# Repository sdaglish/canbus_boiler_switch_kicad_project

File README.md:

# Canbus Boiler Switch KiCad Project

## Version History

* v1.0
    * 23 Feb 2020
        * First manufactured prototype of board
        * Developed for prototyping
        * Developed for extending to sensor, ect. via header pins
* v1.1
    * 23 Feb 2020
        * Adding version history to readme
        * Removed mfr files from project
        * Removed backup files from project
        * Added sheet information to schematic files

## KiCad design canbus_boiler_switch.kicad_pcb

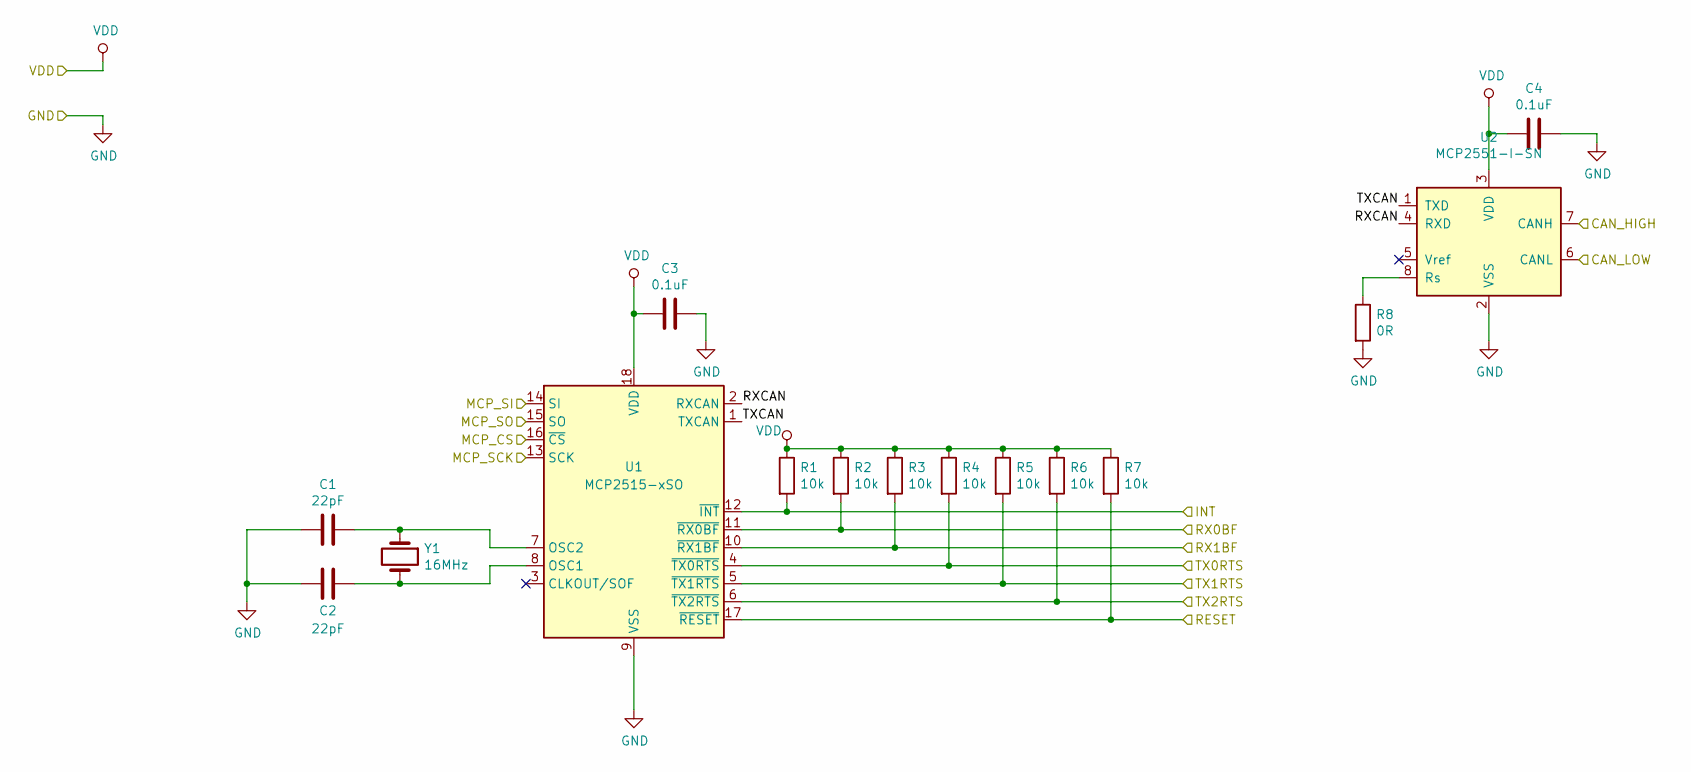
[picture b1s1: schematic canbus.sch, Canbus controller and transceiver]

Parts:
C1, C2: 22pF; C_1206_3216Metric
C3, C4: 0.1uF; C_1206_3216Metric
R1, R2, R3, R4, R5, R6, R7: 10k; R_1206_3216Metric
R8: 0R; R_1206_3216Metric
U1: MCP2515-xSO; SOIC-18W_7.5x11.6mm_P1.27mm
U2: MCP2551-I-SN; SOIC-8_3.9x4.9mm_P1.27mm
Y1: 16MHz; Crystal_SMD_HC49-SD_HandSoldering

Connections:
/canbus/INT: R1.2, U1.12 (~INT); also elsewhere on the board
/canbus/MCP_SCK: U1.13 (SCK); also elsewhere on the board
/canbus/MCP_SI: U1.14 (SI); also elsewhere on the board
/canbus/MCP_SO: U1.15 (SO); also elsewhere on the board
/canbus/RESET: R7.2, U1.17 (~RESET); also elsewhere on the board
/canbus/RX0BF: R2.2, U1.11 (~RX0BF); also elsewhere on the board
/canbus/RX1BF: R3.2, U1.10 (~RX1BF); also elsewhere on the board
/canbus/RXCAN: U1.2 (RXCAN), U2.4 (RXD)
/canbus/TX0RTS: R4.2, U1.4 (~TX0RTS); also elsewhere on the board
/canbus/TX1RTS: R5.2, U1.5 (~TX1RTS); also elsewhere on the board
/canbus/TX2RTS: R6.2, U1.6 (~TX2RTS); also elsewhere on the board
/canbus/TXCAN: U1.1 (TXCAN), U2.1 (TXD)
/mircoprocessor/CS: U1.16 (~CS); also elsewhere on the board
/rj12_connections/CAN_H: U2.7 (CANH); also elsewhere on the board
/rj12_connections/CAN_L: U2.6 (CANL); also elsewhere on the board
GND: C1.2, C2.2, C3.1, C4.1, R8.2, U1.9 (VSS), U2.2 (VSS); also elsewhere on the board
unnamed: C1.1, U1.7 (OSC2), Y1.1
unnamed: C2.1, U1.8 (OSC1), Y1.2
unnamed: R8.1, U2.8 (Rs)
VDD: C3.2, C4.2, R1.1, R2.1, R3.1, R4.1, R5.1, R6.1, R7.1, U1.18 (VDD), U2.3 (VDD); also elsewhere on the board

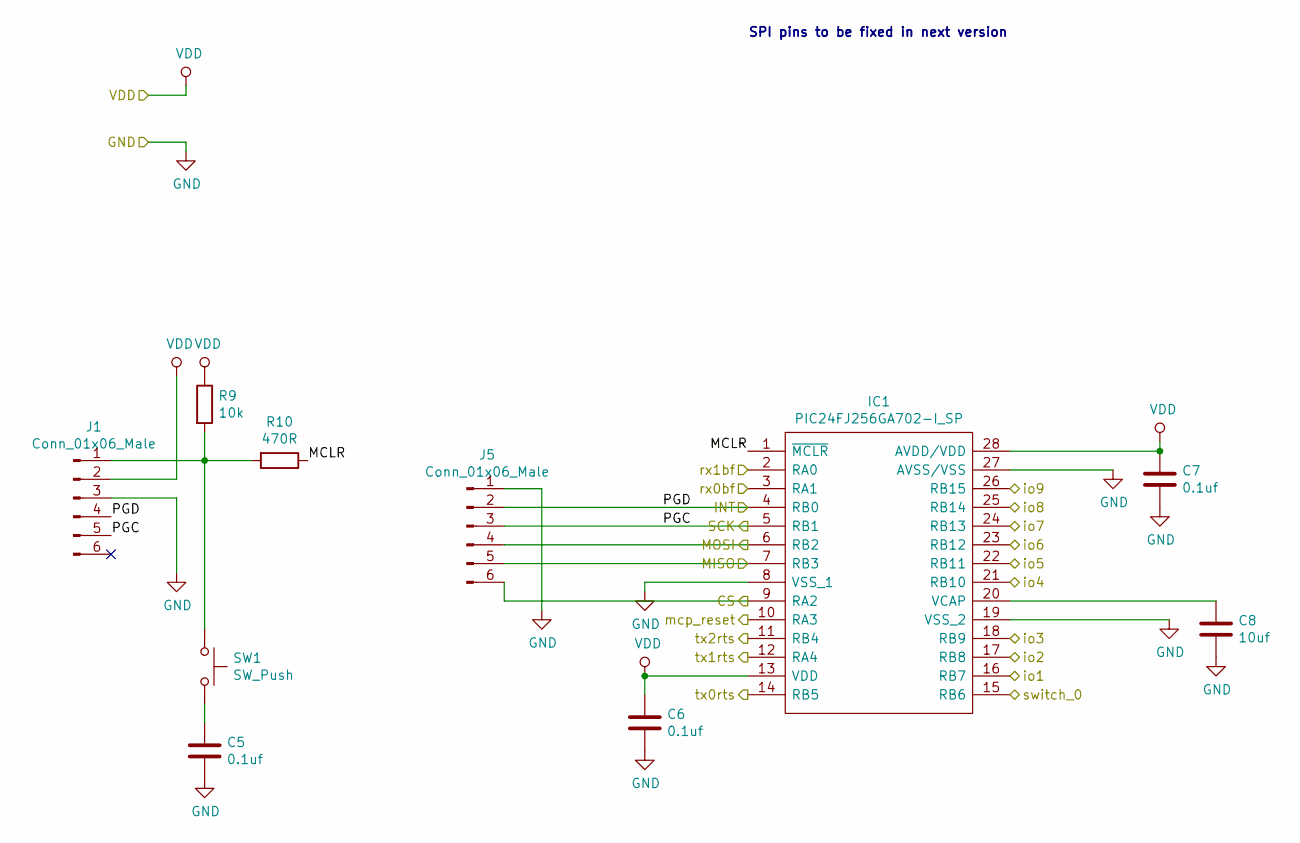
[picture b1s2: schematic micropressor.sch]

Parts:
C5, C6, C7: 0.1uf; C_1206_3216Metric
C8: 10uf; C_1206_3216Metric
IC1: PIC24FJ256GA702-I_SP; SOIC127P1030X265-28N; Manufacturer_Part_Number PIC24FJ256GA702-I/SP; Mouser Part Number 579-24FJ256GA702ISP
J1, J5: Conn_01x06_Male; PinHeader_1x06_P2.54mm_Vertical
R9: 10k; R_1206_3216Metric
R10: 470R; R_1206_3216Metric
SW1: SW_Push; SW_PUSH_6mm

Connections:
/canbus/INT: IC1.4 (RB0), J1.4, J5.2; also elsewhere on the board
/canbus/MCP_SCK: IC1.5 (RB1), J1.5, J5.3; also elsewhere on the board
/canbus/MCP_SI: IC1.6 (RB2), J5.4; also elsewhere on the board
/canbus/MCP_SO: IC1.7 (RB3), J5.5; also elsewhere on the board
/canbus/RESET: IC1.10 (RA3); also elsewhere on the board
/canbus/RX0BF: IC1.3 (RA1); also elsewhere on the board
/canbus/RX1BF: IC1.2 (RA0); also elsewhere on the board
/canbus/TX0RTS: IC1.14 (RB5); also elsewhere on the board
/canbus/TX1RTS: IC1.12 (RA4); also elsewhere on the board
/canbus/TX2RTS: IC1.11 (RB4); also elsewhere on the board
/io/io1: IC1.16 (RB7); also elsewhere on the board
/io/io2: IC1.17 (RB8); also elsewhere on the board
/io/io3: IC1.18 (RB9); also elsewhere on the board
/io/io4: IC1.21 (RB10); also elsewhere on the board
/io/io5: IC1.22 (RB11); also elsewhere on the board
/io/io6: IC1.23 (RB12); also elsewhere on the board
/io/io7: IC1.24 (RB13); also elsewhere on the board
/io/io8: IC1.25 (RB14); also elsewhere on the board
/io/io9: IC1.26 (RB15); also elsewhere on the board
/io/switch_0: IC1.15 (RB6); also elsewhere on the board
/mircoprocessor/CS: IC1.9 (RA2), J5.6; also elsewhere on the board
/mircoprocessor/MCLR: IC1.1 (~MCLR), R10.1
GND: C5.2, C6.2, C7.2, C8.2, IC1.8 (VSS_1), IC1.19 (VSS_2), IC1.27 (AVSS/VSS), J1.3, J5.1; also elsewhere on the board
unnamed: C5.1, SW1.2
unnamed: C8.1, IC1.20 (VCAP)
unnamed: J1.1, R9.2, R10.2, SW1.1
VDD: C6.1, C7.1, IC1.13 (VDD), IC1.28 (AVDD/VDD), J1.2, R9.1; also elsewhere on the board

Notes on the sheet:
SPI pins to be fixed in next version

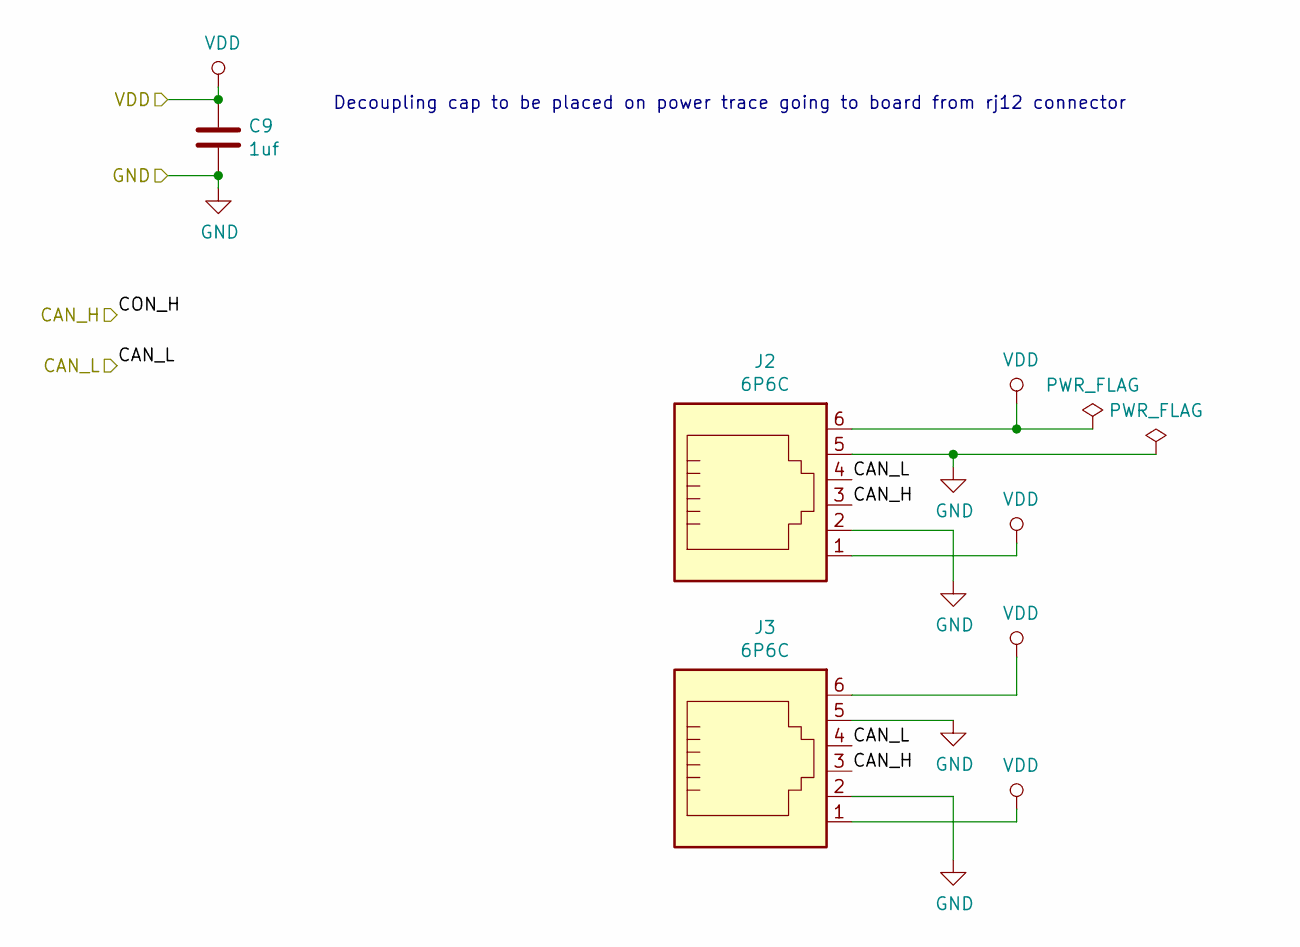
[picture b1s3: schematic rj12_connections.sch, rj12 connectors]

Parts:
C9: 1uf; C_1206_3216Metric
J2, J3: 6P6C; RJ12_Amphenol_54601

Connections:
/rj12_connections/CAN_H: J2.3, J3.3; also elsewhere on the board
/rj12_connections/CAN_L: J2.4, J3.4; also elsewhere on the board
GND: C9.2, J2.2, J2.5, J3.2, J3.5; also elsewhere on the board
VDD: C9.1, J2.1, J2.6, J3.1, J3.6; also elsewhere on the board

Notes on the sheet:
Decoupling cap to be placed on power trace going to board from rj12 connector

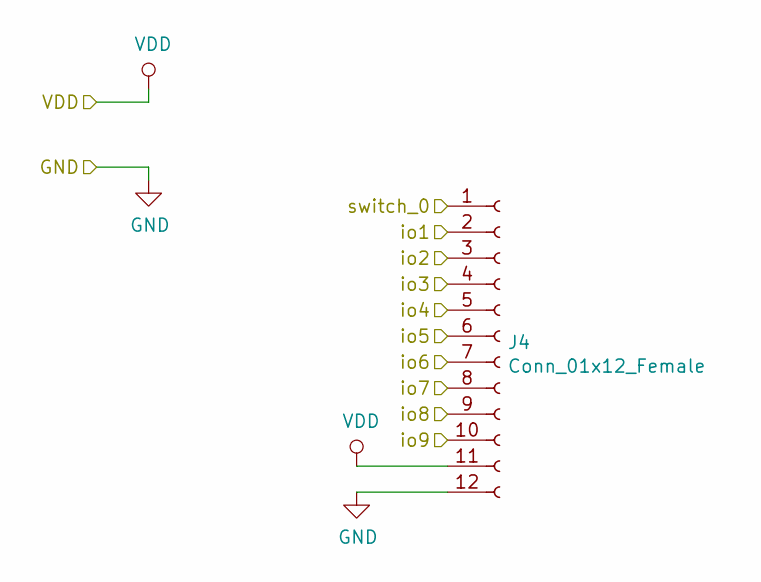
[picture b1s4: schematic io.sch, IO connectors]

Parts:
J4: Conn_01x12_Female; PinSocket_1x12_P2.54mm_Vertical

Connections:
/io/io1: J4.2; also elsewhere on the board
/io/io2: J4.3; also elsewhere on the board
/io/io3: J4.4; also elsewhere on the board
/io/io4: J4.5; also elsewhere on the board
/io/io5: J4.6; also elsewhere on the board
/io/io6: J4.7; also elsewhere on the board
/io/io7: J4.8; also elsewhere on the board
/io/io8: J4.9; also elsewhere on the board
/io/io9: J4.10; also elsewhere on the board
/io/switch_0: J4.1; also elsewhere on the board
GND: J4.12; also elsewhere on the board
VDD: J4.11; also elsewhere on the board

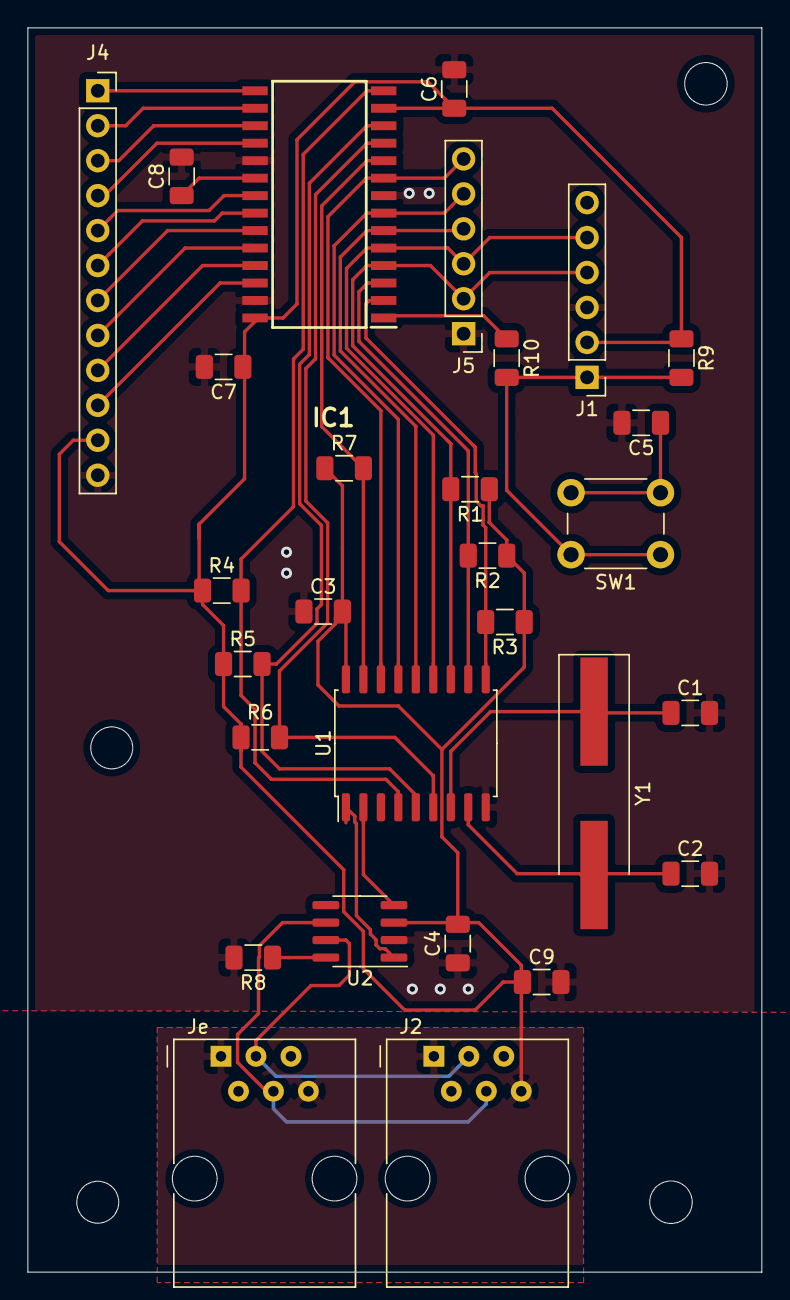
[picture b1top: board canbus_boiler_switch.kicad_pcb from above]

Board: 2 copper layers, 53.3 x 90.4 mm, 29 parts (0 on the bottom side), 34 nets.

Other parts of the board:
Je: 6P6C; RJ12_Amphenol_54601

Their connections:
/rj12_connections/CAN_H: Je.3; also elsewhere on the board
/rj12_connections/CAN_L: Je.4; also elsewhere on the board
GND: Je.2, Je.5; also elsewhere on the board
VDD: Je.1, Je.6; also elsewhere on the board

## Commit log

2019-10-19 Project creation
2020-02-23 Finishing up
2020-02-23 Added schematic notes
2020-02-23 Adding release information on schematic errors
2020-02-23 Page setting information added
2020-02-23 Plot files added
2020-02-23 grb files removed from project
2020-02-23 mfr files removed from project
2020-02-23 Version history added to README
2020-02-23 Removing mfr files
2020-02-23 Added mfr files
2020-02-23 Added swp files
2020-02-23 Removed bak files
2020-02-23 Added bak files back to ignore
2020-02-23 Deleted backup files from git
2020-02-23 Added *.sch-bak files
2020-02-23 Deleted swp files from git
2020-02-23 Version history added
2020-02-23 Fixing bullet points
2020-02-23 Added version history
2020-02-23 Added unneeded zip files
2020-02-24 Further page information added to schematic sheets
2020-02-24 Added page information to pcb sheet
2020-02-24 Note added to fix SPI pin in next revision
